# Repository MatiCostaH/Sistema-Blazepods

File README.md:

# Sistema-Blazepods
Trabajo Práctico principal de la cátedra Tecnología Electrónica. En el mismo el objetivo es crear un dispostivo capaz de medir los tiempos de acción y reacción de las personas. Sus principales aplicaciones estan ligadas a lo deportivo, con la posibilidad de ampliarlo a usos médicos más sensibles.

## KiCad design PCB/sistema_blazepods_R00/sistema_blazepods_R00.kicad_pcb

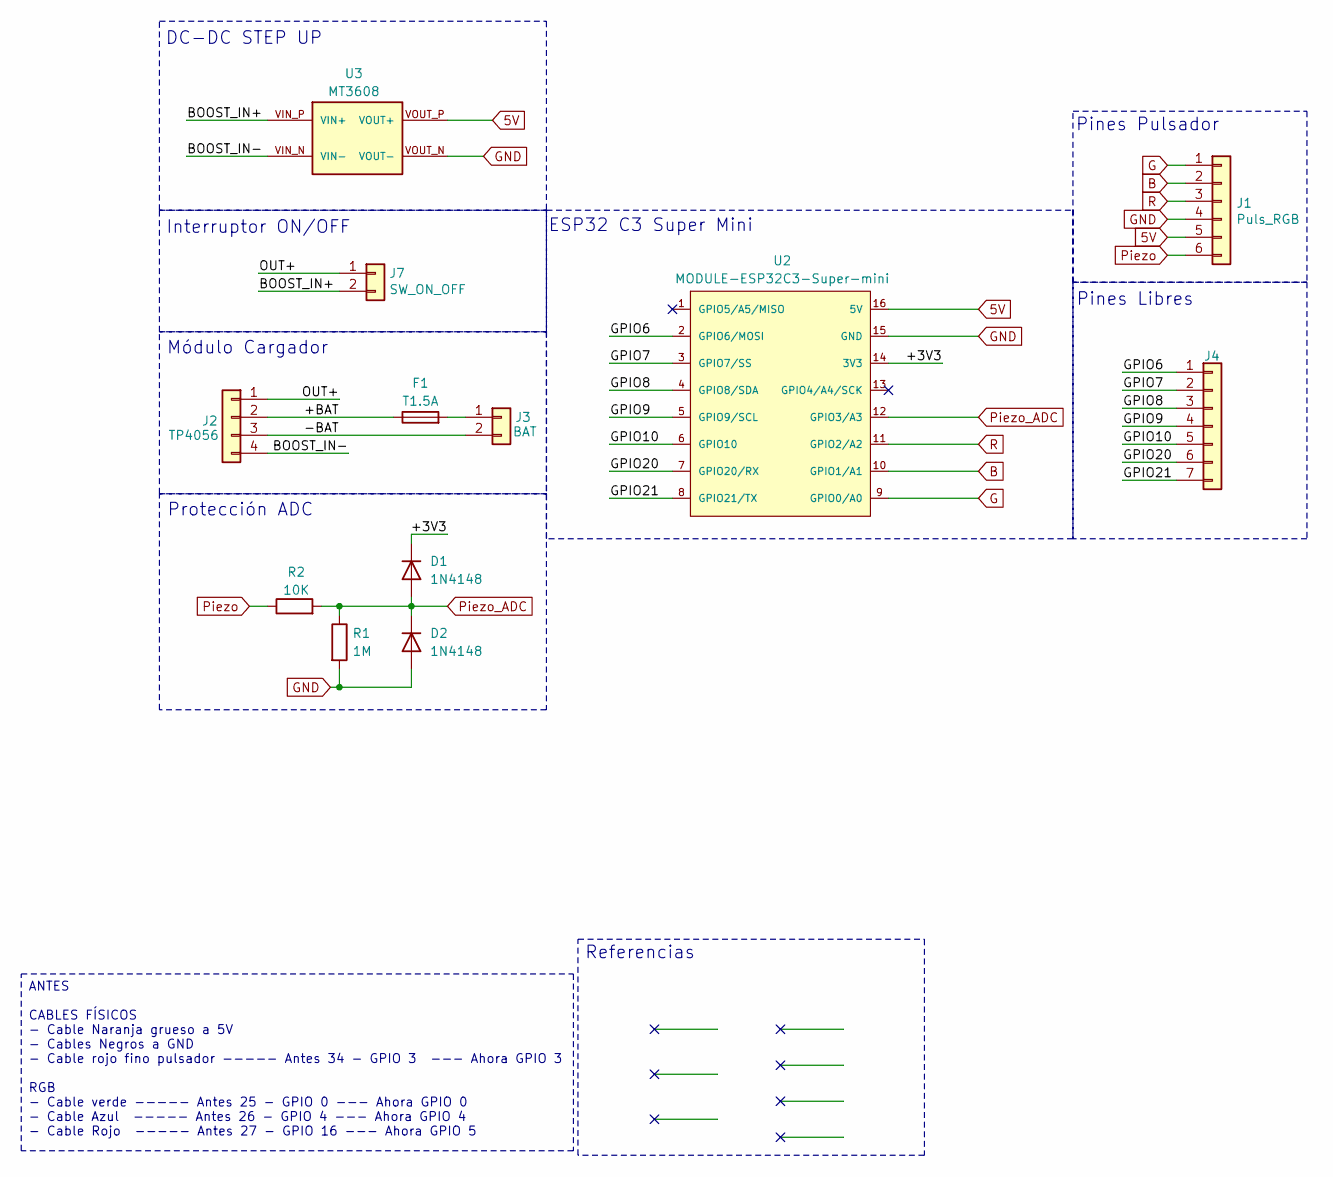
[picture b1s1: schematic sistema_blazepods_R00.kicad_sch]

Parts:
D1, D2: 1N4148; D_DO-41_SOD81_P10.16mm_Horizontal
F1: T1.5A; Fuseholder_Cylinder-5x20mm_Schurter_0031_8201_Horizontal_Op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
J1: Puls_RGB; PinHeader_1x06_P2.54mm_Vertical
J2: TP4056; PinHeader_1x04_P2.54mm_Vertical
J3: BAT; PinHeader_1x02_P2.54mm_Vertical
J4: Conn_01x07; PinHeader_1x07_P2.54mm_Vertical
J7: SW_ON_OFF; PinHeader_1x02_P2.54mm_Vertical
R1: 1M; R_Axial_DIN0207_L6.3mm_D2.5mm_P10.16mm_Horizontal
R2: 10K; R_Axial_DIN0207_L6.3mm_D2.5mm_P10.16mm_Horizontal
U2: MODULE-ESP32C3-Super-mini; MODULE_ESP32-C3_SUPERMINI_TH
U3: MT3608; MODULE_MT3608_DC-DC_STEP_UP_CONVERTER_2A_BOOSTER_MODULE

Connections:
5V: J1.5, U2.16 (5V), U3.VOUT_P (VOUT+)
/+3V3: D1.1 (K), U2.14 (3V3)
/+BAT: F1.1, J2.2
/-BAT: J2.3, J3.2
/BOOST_IN+: J7.2, U3.VIN_P (VIN+)
/BOOST_IN-: J2.4, U3.VIN_N (VIN-)
/GPIO6: J4.1, U2.2 (GPIO6/MOSI)
/GPIO7: J4.2, U2.3 (GPIO7/SS)
/GPIO8: J4.3, U2.4 (GPIO8/SDA)
/GPIO9: J4.4, U2.5 (GPIO9/SCL)
/GPIO10: J4.5, U2.6 (GPIO10)
/GPIO20: J4.6, U2.7 (GPIO20/RX)
/GPIO21: J4.7, U2.8 (GPIO21/TX)
/OUT+: J2.1, J7.1
B: J1.2, U2.10 (GPIO1/A1)
G: J1.1, U2.9 (GPIO0/A0)
GND: D2.2 (A), J1.4, R1.2, U2.15 (GND), U3.VOUT_N (VOUT-)
unnamed: F1.2, J3.1
Piezo: J1.6, R2.1
Piezo_ADC: D1.2 (A), D2.1 (K), R1.1, R2.2, U2.12 (GPIO3/A3)
R: J1.3, U2.11 (GPIO2/A2)

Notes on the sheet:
ESP32 C3 Super Mini
Protección ADC
Interruptor ON/OFF
Pines Pulsador
Pines Libres
DC-DC STEP UP
Módulo Cargador
Referencias
ANTES CABLES FÍSICOS - Cable Naranja grueso a 5V - Cables Negros a GND - Cable rojo fino pulsador ----- Antes 34 - GPIO 3 --- Ahora GPIO 3 RGB - Cable verde ----- Antes 25 - GPIO 0 --- Ahora GPIO 0 - Cable Azul ----- Antes 26 - GPIO 4 --- Ahora GPIO 4 - Cable Rojo ----- Antes 27 - GPIO 16 --- Ahora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

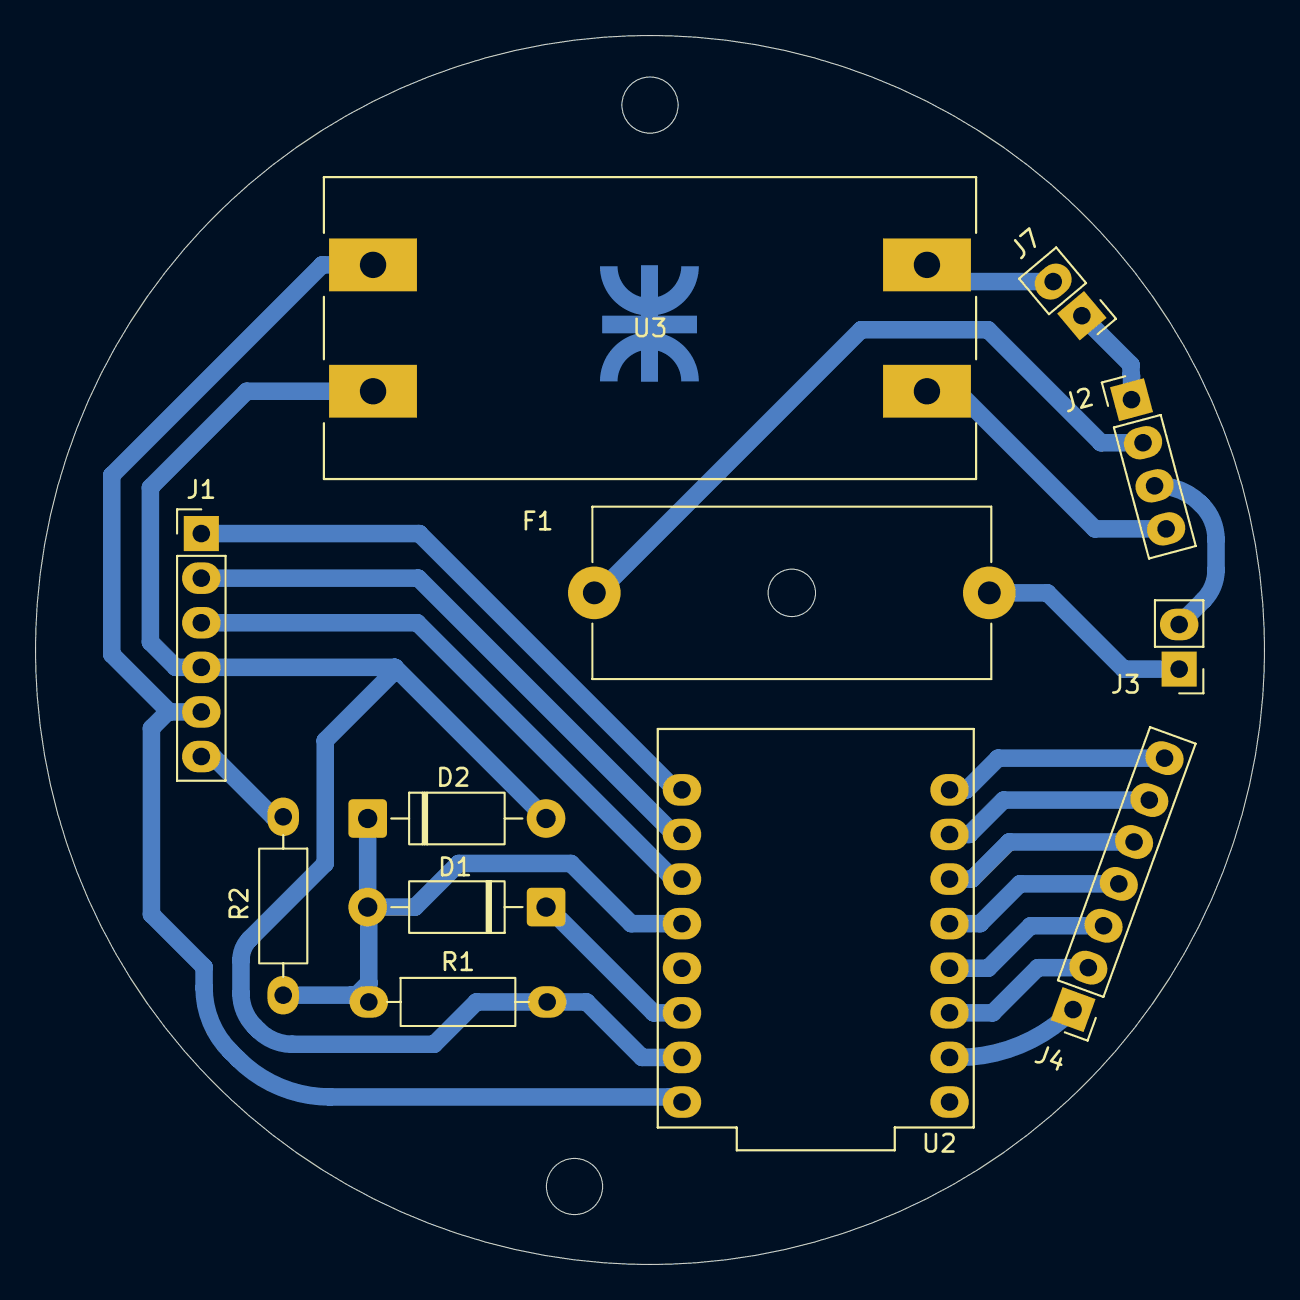
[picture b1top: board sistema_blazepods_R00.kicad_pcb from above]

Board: 2 copper layers, 70.0 x 70.0 mm, 12 parts (0 on the bottom side), 21 nets.
